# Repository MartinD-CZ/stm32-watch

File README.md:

# stm32-watch

*see the article [here](http://embedblog.eu/?p=34)!*

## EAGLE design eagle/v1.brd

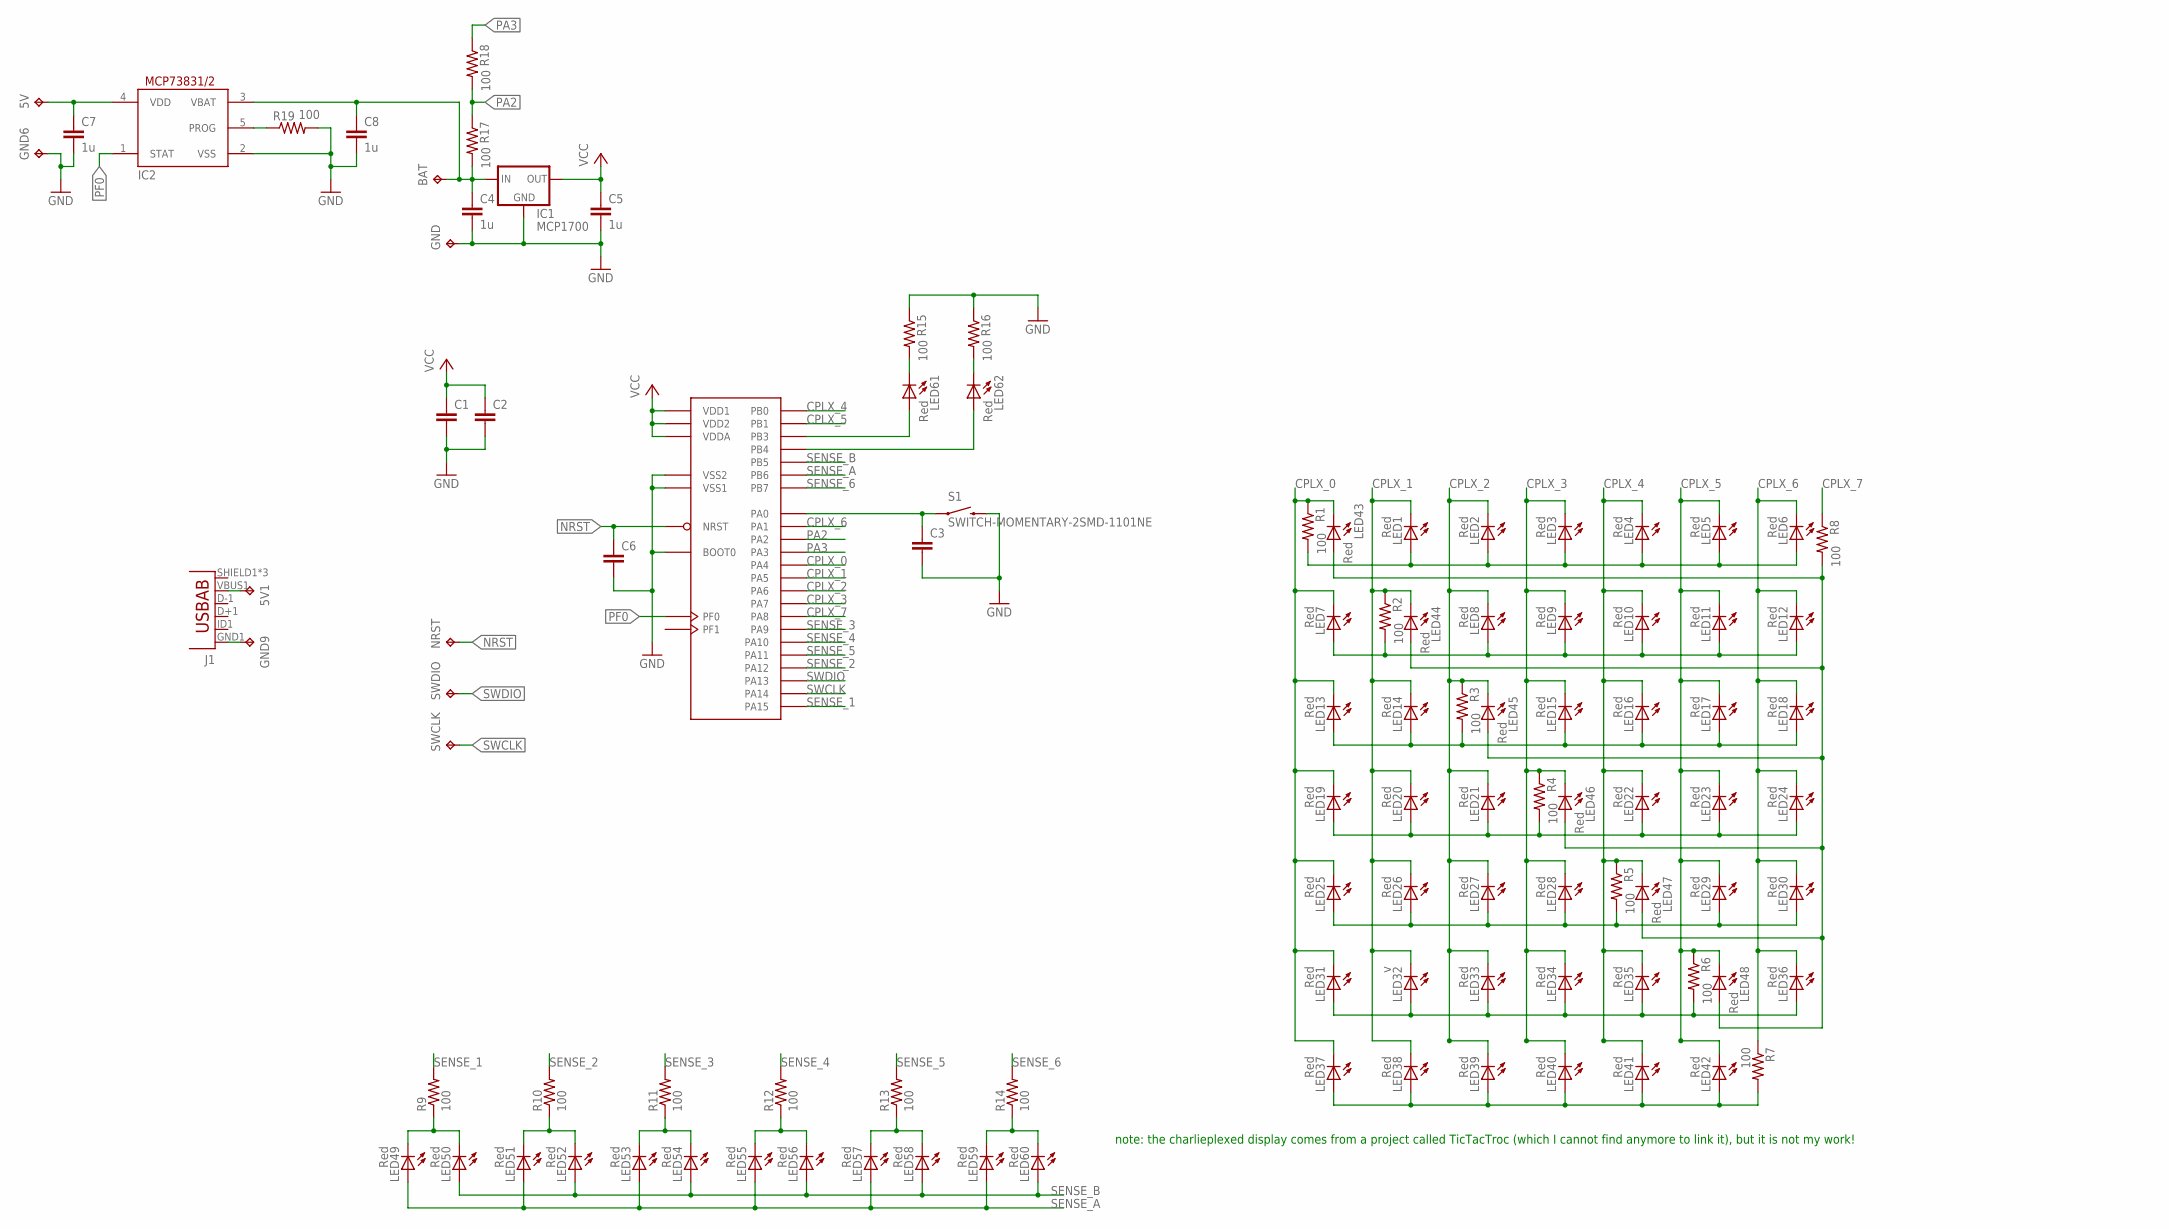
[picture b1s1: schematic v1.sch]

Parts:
5V, 5V1: TPB1,27; B1,27
BAT: TPB1,27; B1,27
C1, C2, C3, C6: C-EUC0603K; C0603K
C4, C5, C7, C8: 1u; C0603K
GND, GND6, GND9: TPB1,27; B1,27
IC1: MCP1700; SOT23
IC2: MCP73831/OT; SOT23-5L
J1: USB-ABCONN-11794; USB-AB-MICRO-SMD_V03
LED1, LED2, LED3, LED4, LED5, LED6, LED7, LED8, LED9, LED10, LED11, LED12, LED13, LED14, LED15, LED16, LED17, LED18, LED19, LED20, LED21, LED22, LED23, LED24, LED25, LED26, LED27, LED28, LED29, LED30, LED31, LED33, LED34, LED35, LED36, LED37, LED38, LED39, LED40, LED41, LED42, LED43, LED44, LED45, LED46, LED47, LED48, LED49, LED50, LED51, LED52, LED53, LED54, LED55, LED56, LED57, LED58, LED59, LED60, LED61, LED62: Red; LED-0603
LED32: v; LED-0603
NRST: TPB1,27; B1,27
R1, R2, R3, R4, R5, R6, R7, R8, R9, R10, R11, R12, R13, R14, R15, R16, R17, R18, R19: 100; 0402-RES
S1: SWITCH-MOMENTARY-2SMD-1101NE; TACTILE-SWITCH-1101NE
SWCLK: TPB1,27; B1,27
SWDIO: TPB1,27; B1,27
U$1: STM32F030K6T6; TQFP32-08

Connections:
CPLX_0: LED7.C, LED13.C, LED19.C, LED25.C, LED31.C, LED37.C, LED43.C, R1.1, U$1.10 (PA4)
CPLX_1: LED1.C, LED14.C, LED20.C, LED26.C, LED32.C, LED38.C, LED44.C, R2.1, U$1.11 (PA5)
CPLX_2: LED2.C, LED8.C, LED21.C, LED27.C, LED33.C, LED39.C, LED45.C, R3.1, U$1.12 (PA6)
CPLX_3: LED3.C, LED9.C, LED15.C, LED28.C, LED34.C, LED40.C, LED46.C, R4.1, U$1.13 (PA7)
CPLX_4: LED4.C, LED10.C, LED16.C, LED22.C, LED35.C, LED41.C, LED47.C, R5.1, U$1.14 (PB0)
CPLX_5: LED5.C, LED11.C, LED17.C, LED23.C, LED29.C, LED42.C, LED48.C, R6.1, U$1.15 (PB1)
CPLX_6: LED6.C, LED12.C, LED18.C, LED24.C, LED30.C, LED36.C, R7.1, U$1.7 (PA1)
CPLX_7: R8.1, U$1.18 (PA8)
GND: C1.2, C2.2, C3.2, C4.2, C5.2, C6.2, C7.2, C8.2, GND.TP, GND6.TP, IC1.1 (GND), IC2.2 (VSS), R15.1, R16.1, R19.2, S1.2, U$1.16 (VSS1), U$1.31 (BOOT0), U$1.32 (VSS2)
unnamed: LED61.A, U$1.26 (PB3)
unnamed: LED62.A, U$1.27 (PB4)
unnamed: GND9.TP, J1.GND1 (GND)
unnamed: C3.1, S1.1, U$1.6 (PA0)
unnamed: LED61.C, R15.2
unnamed: LED62.C, R16.2
unnamed: 5V1.TP, J1.VBUS1 (VBUS)
unnamed: 5V.TP, C7.1, IC2.4 (VDD)
unnamed: IC2.5 (PROG), R19.1
unnamed: BAT.TP, C4.1, C8.1, IC1.3 (IN), IC2.3 (VBAT), R17.2
unnamed: LED19.A, LED20.A, LED21.A, LED22.A, LED23.A, LED24.A, R4.2
unnamed: LED1.A, LED2.A, LED3.A, LED4.A, LED5.A, LED6.A, R1.2
unnamed: LED7.A, LED8.A, LED9.A, LED10.A, LED11.A, LED12.A, R2.2
unnamed: LED25.A, LED26.A, LED27.A, LED28.A, LED29.A, LED30.A, R5.2
unnamed: LED13.A, LED14.A, LED15.A, LED16.A, LED17.A, LED18.A, R3.2
unnamed: LED43.A, LED44.A, LED45.A, LED46.A, LED47.A, LED48.A, R8.2
unnamed: LED37.A, LED38.A, LED39.A, LED40.A, LED41.A, LED42.A, R7.2
unnamed: LED31.A, LED32.A, LED33.A, LED34.A, LED35.A, LED36.A, R6.2
unnamed: LED49.C, LED50.C, R9.1
unnamed: LED51.C, LED52.C, R10.1
unnamed: LED53.C, LED54.C, R11.1
unnamed: LED55.C, LED56.C, R12.1
unnamed: LED57.C, LED58.C, R13.1
unnamed: LED59.C, LED60.C, R14.1
NRST: C6.1, NRST.TP, U$1.4 (NRST)
PA2: R17.1, R18.2, U$1.8 (PA2)
PA3: R18.1, U$1.9 (PA3)
PF0: IC2.1 (STAT), U$1.2 (PF0)
SENSE_1: R9.2, U$1.25 (PA15)
SENSE_2: R10.2, U$1.22 (PA12)
SENSE_3: R11.2, U$1.19 (PA9)
SENSE_4: R12.2, U$1.20 (PA10)
SENSE_5: R13.2, U$1.21 (PA11)
SENSE_6: R14.2, U$1.30 (PB7)
SENSE_A: LED49.A, LED51.A, LED53.A, LED55.A, LED57.A, LED59.A, U$1.29 (PB6)
SENSE_B: LED50.A, LED52.A, LED54.A, LED56.A, LED58.A, LED60.A, U$1.28 (PB5)
SWCLK: SWCLK.TP, U$1.24 (PA14)
SWDIO: SWDIO.TP, U$1.23 (PA13)
VCC: C1.1, C2.1, C5.1, IC1.2 (OUT), U$1.1 (VDD1), U$1.5 (VDDA), U$1.17 (VDD2)

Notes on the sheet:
note: the charlieplexed display comes from a project called TicTacTroc (which I cannot find anymore to link it), but it is not my work!

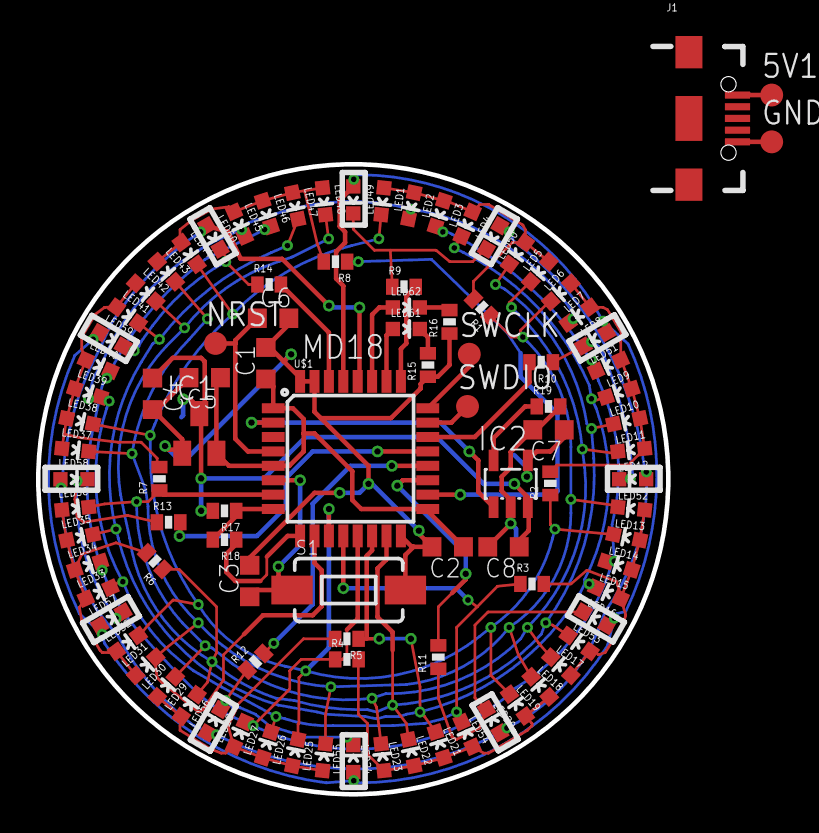
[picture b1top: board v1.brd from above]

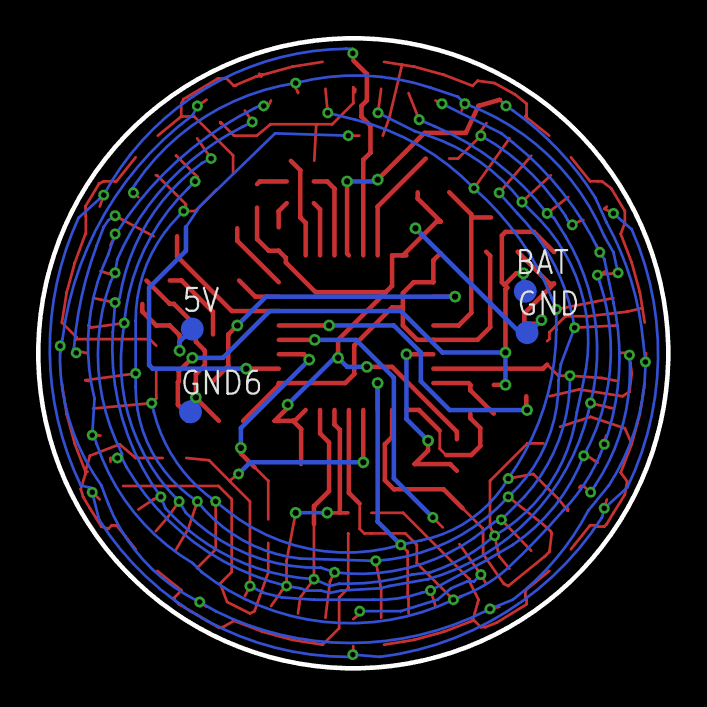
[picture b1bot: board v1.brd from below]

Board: 2 copper layers, 35.0 x 35.0 mm, 103 parts (4 on the bottom side), 48 nets.

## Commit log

2018-11-11 initial

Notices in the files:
parts and their libraries:
SparkFun-DigitalIC: Licensing: Creative Commons ShareAlike 4.0 International - https://creativecommons.org/licenses/by-sa/4.0
